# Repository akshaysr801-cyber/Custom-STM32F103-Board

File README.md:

# Custom STM32F103 Board

A custom printed circuit board (PCB) design based on the STM32F103 microcontroller. The schematic and board layout were created using KiCad.

## Project status

PCB design files are available. Fabrication and hardware testing status: [add status].

## Files

- `Custom_STM32103.kicad_sch` — circuit schematic
- `Custom_STM32103.kicad_pcb` — PCB layout
- `board-layout.png` — screenshot of the design

## Tools

- KiCad
- STM32F103 microcontroller

## Notes

This project is for learning and development. Review the schematic and PCB layout before manufacturing or using the board.

## Author

Akshay

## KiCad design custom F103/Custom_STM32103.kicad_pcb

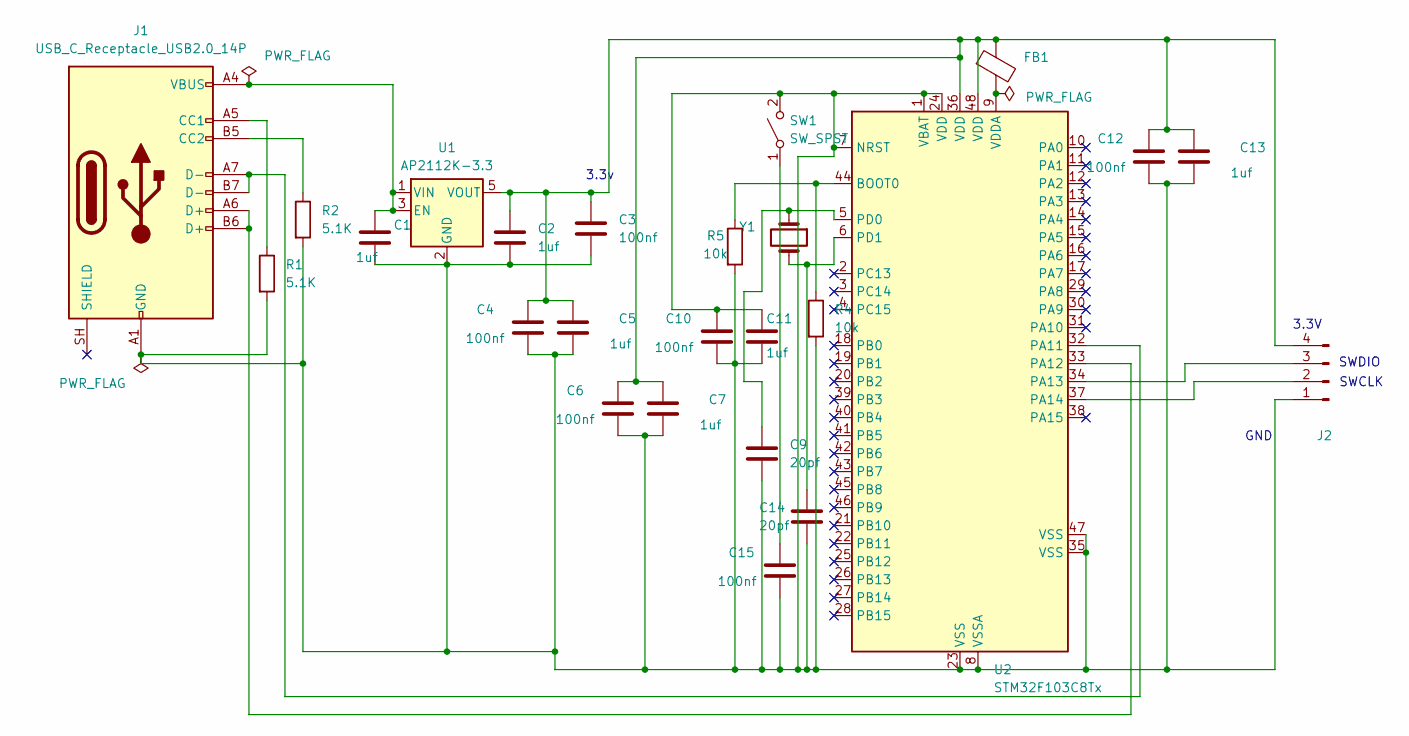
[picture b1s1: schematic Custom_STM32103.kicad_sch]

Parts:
C1, C2, C5, C7, C11, C13: 1uf; C_0402_1005Metric
C3, C4, C6, C10, C12, C15: 100nf; C_0402_1005Metric
C9, C14: 20pf; C_0402_1005Metric
FB1: FerriteBead; L_0805_2012Metric
J1: USB_C_Receptacle_USB2.0_14P; USB_C_Receptacle_Amphenol_124019772112A
J2: Conn_01x04_Pin; PinHeader_1x04_P2.54mm_Vertical_SMD_Pin1Right
R1, R2: 5.1K; R_0603_1608Metric
R4, R5: 10k; R_0603_1608Metric
SW1: SW_SPST; SW_SPST_TL3342
U1: AP2112K-3.3; SOT-23-5
U2: STM32F103C8Tx; LQFP-48_7x7mm_P0.5mm
Y1: 8MHZ; Crystal_HC49-4H_Vertical

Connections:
unnamed: J1.A5 (CC1), R1.1
unnamed: J1.B5 (CC2), R2.1
unnamed: C1.2, C2.2, C3.2, C4.2, C5.2, C6.2, C7.2, C9.2, C10.1, C10.2, C11.1, C11.2, C12.2, C13.2, C14.2, C15.2, J1.A1 (GND), J1.A12 (GND), J1.B1 (GND), J1.B12 (GND), J2.1, R1.2, R2.2, R4.2, R5.2, SW1.2 (B), U1.2 (GND), U2.1 (VBAT), U2.7 (NRST), U2.8 (VSSA), U2.23 (VSS), U2.24 (VDD), U2.35 (VSS), U2.47 (VSS)
unnamed: J2.2, U2.37 (PA14)
unnamed: J2.3, U2.34 (PA13)
unnamed: C2.1, C3.1, C4.1, C5.1, C6.1, C7.1, C12.1, C13.1, FB1.1, J2.4, U1.5 (VOUT), U2.36 (VDD), U2.48 (VDD)
unnamed: C15.1, SW1.1 (A)
unnamed: C1.1, J1.A4 (VBUS), J1.A9 (VBUS), J1.B4 (VBUS), J1.B9 (VBUS), U1.1 (VIN), U1.3 (EN)
unnamed: R4.1, R5.1, U2.44 (BOOT0)
unnamed: J1.A7 (D-), J1.B7 (D-), U2.32 (PA11)
unnamed: J1.A6 (D+), J1.B6 (D+), U2.33 (PA12)
unnamed: C9.1, U2.5 (PD0), Y1.1
unnamed: C14.1, U2.6 (PD1), Y1.2
unnamed: FB1.2, U2.9 (VDDA)

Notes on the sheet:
GND
3.3V
SWCLK
SWDIO
3.3v

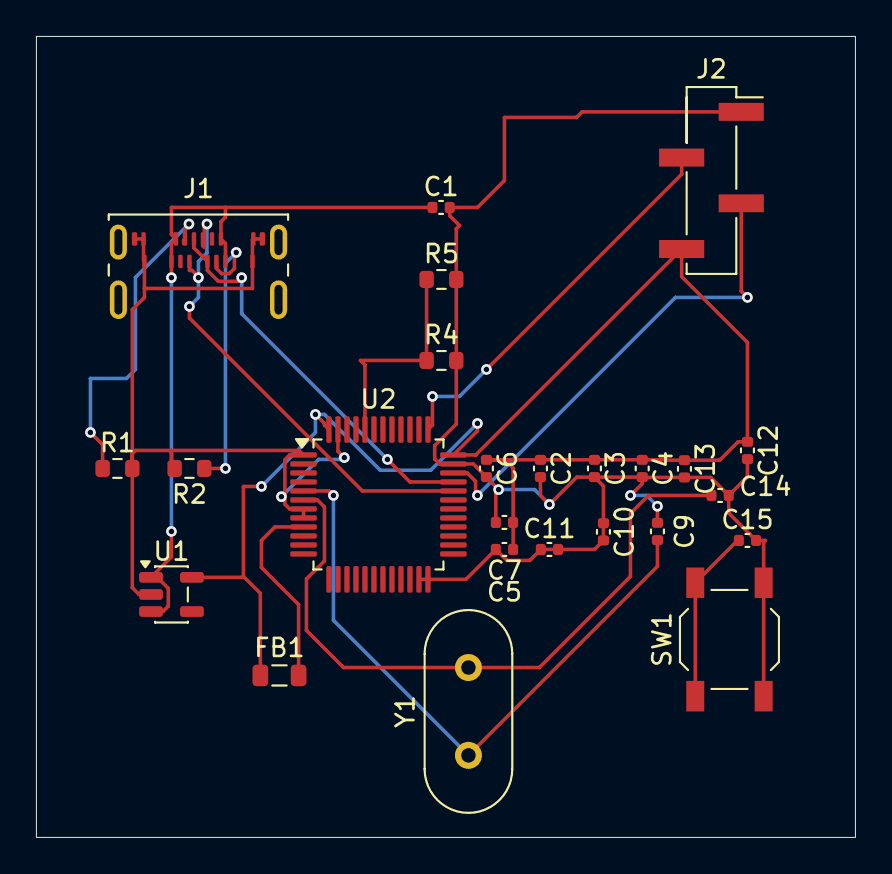
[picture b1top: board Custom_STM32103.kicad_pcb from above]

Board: 2 copper layers, 45.5 x 44.5 mm, 25 parts (0 on the bottom side), 14 nets.
